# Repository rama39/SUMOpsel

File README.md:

# SUMOpsel
Projeto de eletrônica do processo seletivo do Maracatronics 2024.2/2025.1

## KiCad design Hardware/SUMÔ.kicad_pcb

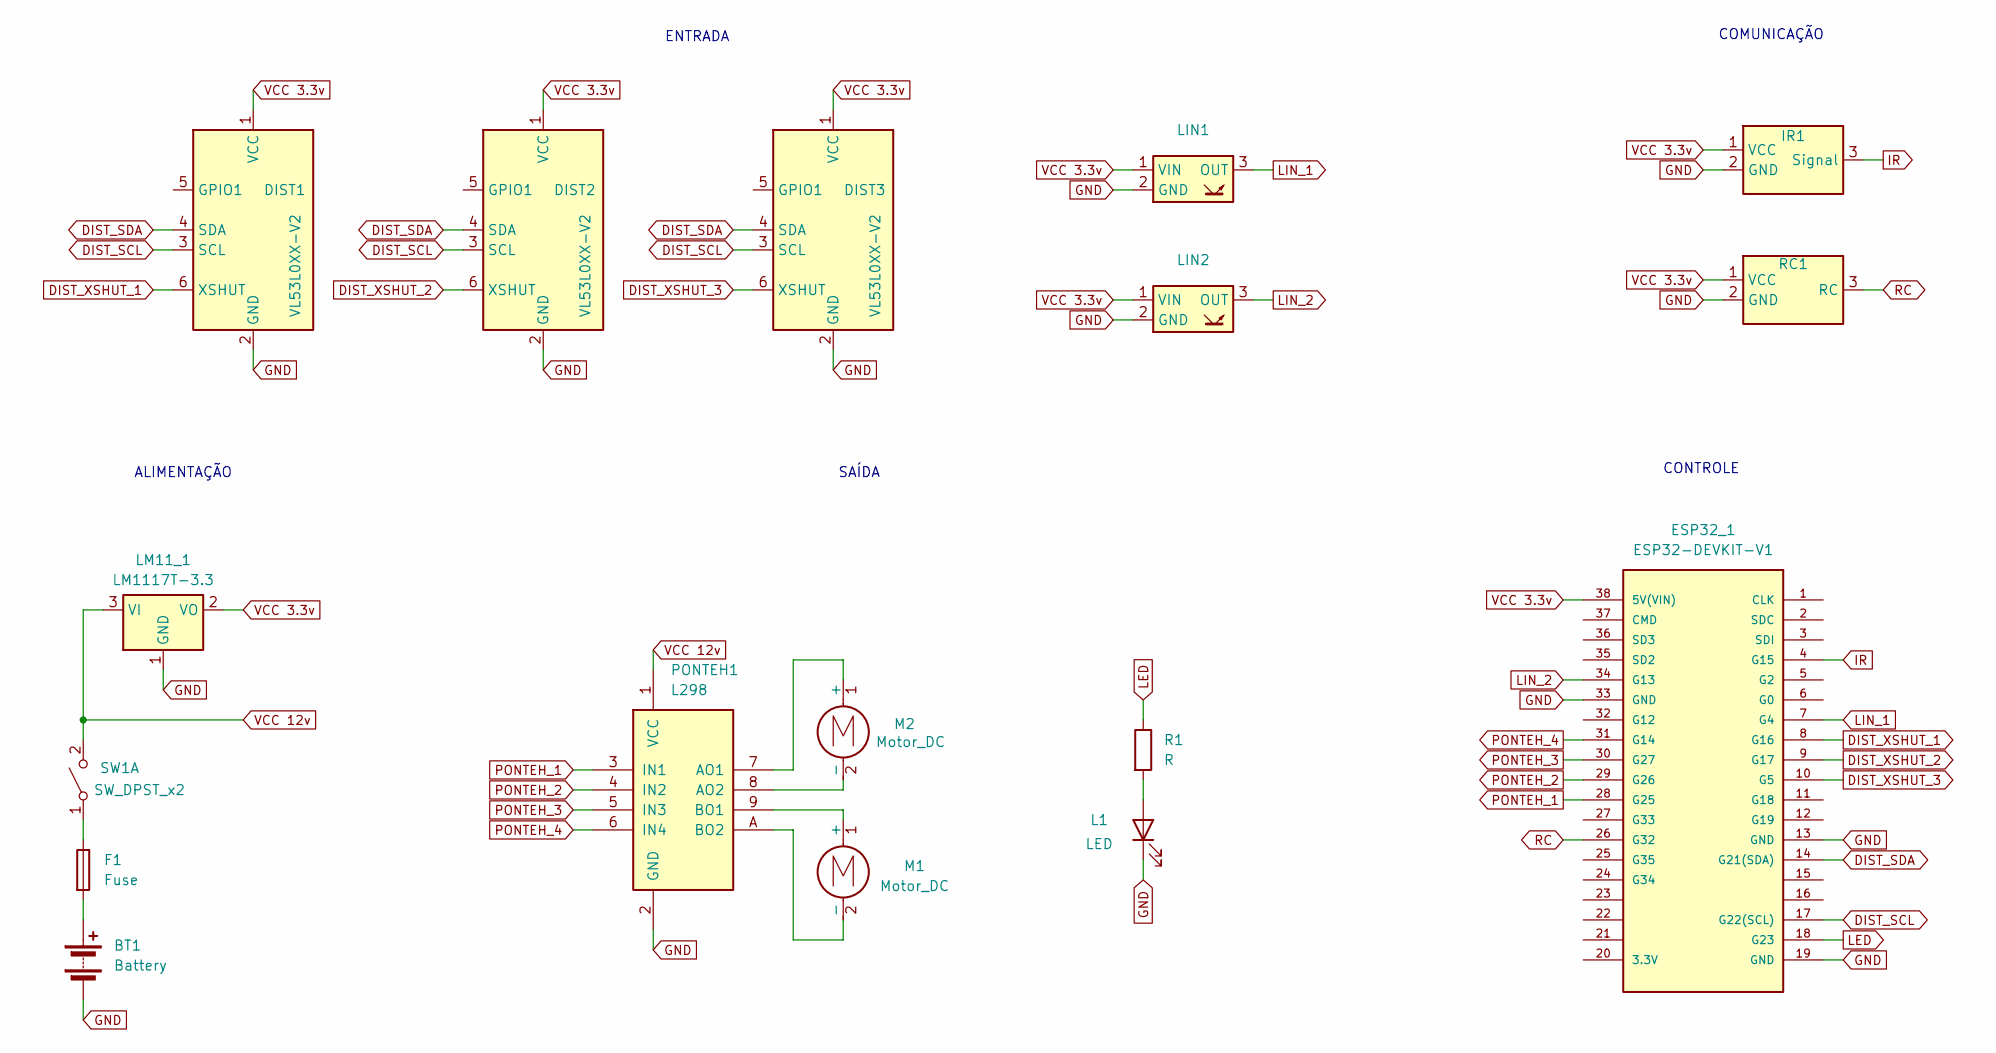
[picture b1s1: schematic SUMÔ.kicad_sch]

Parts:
BT1: Battery; PinHeader_1x02_P2.54mm_Vertical
DIST1, DIST2, DIST3: VL53L0XX-V2; Vl53l0x_custom
ESP32_1: ESP32-DEVKIT-V1; MODULE_ESP32_DEVKIT_V1; PARTREV N/A
F1: Fuse; Fuseholder_Clip-5x20mm_Littelfuse_100_Inline_P20.50x4.60mm_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
IR1: KY022_custom
L1: LED; LED_D3.0mm
LIN1, LIN2: QRE1113_custom
LM11_1: LM1117T-3.3; TO-220-3_Vertical
M1, M2: Motor_DC; PinHeader_1x02_P2.54mm_Vertical
PONTEH1: L298; PONTEH_custom
R1: R; R_Axial_DIN0204_L3.6mm_D1.6mm_P7.62mm_Horizontal
RC1: RC_custom
SW1: SW_DPST_x2; PinHeader_1x02_P2.54mm_Vertical

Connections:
DIST_SCL: DIST1.3 (SCL), DIST2.3 (SCL), DIST3.3 (SCL), ESP32_1.17 (G22(SCL))
DIST_SDA: DIST1.4 (SDA), DIST2.4 (SDA), DIST3.4 (SDA), ESP32_1.14 (G21(SDA))
DIST_XSHUT_1: DIST1.6 (XSHUT), ESP32_1.8 (G16)
DIST_XSHUT_2: DIST2.6 (XSHUT), ESP32_1.9 (G17)
DIST_XSHUT_3: DIST3.6 (XSHUT), ESP32_1.10 (G5)
GND: BT1.2 (-), DIST1.2 (GND), DIST2.2 (GND), DIST3.2 (GND), ESP32_1.13 (GND), ESP32_1.19 (GND), ESP32_1.33 (GND), IR1.2 (GND), L1.1 (K), LIN1.2 (GND), LIN2.2 (GND), LM11_1.1 (GND), PONTEH1.2 (GND), RC1.2 (GND)
IR: ESP32_1.4 (G15), IR1.3 (Signal)
LED: ESP32_1.18 (G23), R1.1
LIN_1: ESP32_1.7 (G4), LIN1.3 (OUT)
LIN_2: ESP32_1.34 (G13), LIN2.3 (OUT)
unnamed: BT1.1 (+), F1.2
unnamed: L1.2 (A), R1.2
unnamed: M1.1 (+), PONTEH1.9 (BO1)
unnamed: M1.2 (-), PONTEH1.A (BO2)
unnamed: M2.1 (+), PONTEH1.7 (AO1)
unnamed: M2.2 (-), PONTEH1.8 (AO2)
unnamed: F1.1, SW1.1 (A)
PONTEH_1: ESP32_1.28 (G25), PONTEH1.3 (IN1)
PONTEH_2: ESP32_1.29 (G26), PONTEH1.4 (IN2)
PONTEH_3: ESP32_1.30 (G27), PONTEH1.5 (IN3)
PONTEH_4: ESP32_1.31 (G14), PONTEH1.6 (IN4)
RC: ESP32_1.26 (G32), RC1.3 (RC)
VCC 3.3v: DIST1.1 (VCC), DIST2.1 (VCC), DIST3.1 (VCC), ESP32_1.38 (5V(VIN)), IR1.1 (VCC), LIN1.1 (VIN), LIN2.1 (VIN), LM11_1.2 (VO), RC1.1 (VCC)
VCC 12v: LM11_1.3 (VI), PONTEH1.1 (VCC), SW1.2 (B)

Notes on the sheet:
CONTROLE
SAÍDA
ENTRADA
ALIMENTAÇÃO
COMUNICAÇÃO

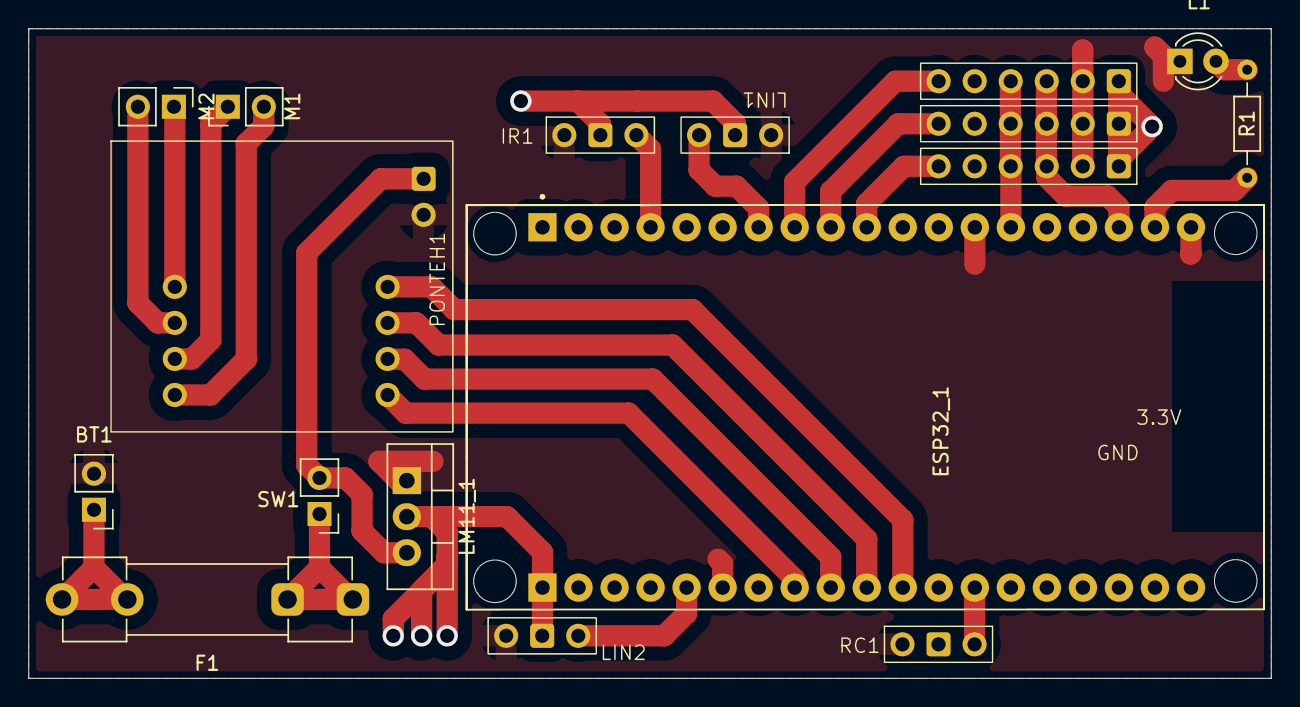
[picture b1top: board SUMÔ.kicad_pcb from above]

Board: 2 copper layers, 87.6 x 45.8 mm, 17 parts (0 on the bottom side), 24 nets.

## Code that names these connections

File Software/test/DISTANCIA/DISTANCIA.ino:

//================================================================================================
// Biblio dos VL53L0X
/*
  Biblioteca que controla a incialização e leitura de três sensores TOF VL53L0X
*/

// pin number 
#define DIST_XSHUT_1 5
#define DIST_XSHUT_2 17
#define DIST_XSHUT_3 16

// Usa biblioteca Adafruit como base
#include "Adafruit_VL53L0X.h"

// address we will assign sensors
#define LOX1_ADDRESS 0x30
#define LOX2_ADDRESS 0x31
#define LOX3_ADDRESS 0x32

void setupDist();

void setID();
void readSensores(bool);

//------------------------------------------------------------------------------------------------
/*
  Quase igual ao código encontrado em:
  https://github.com/adafruit/Adafruit_VL53L0X/blob/master/examples/vl53l0x_dual/vl53l0x_dual.ino
  <3 obg comunidade open source 🤝 <3
*/

// objects for the vl53l0x
Adafruit_VL53L0X lox1 = Adafruit_VL53L0X();
Adafruit_VL53L0X lox2 = Adafruit_VL53L0X();
Adafruit_VL53L0X lox3 = Adafruit_VL53L0X();

// this holds the measurement
VL53L0X_RangingMeasurementData_t measure1;
VL53L0X_RangingMeasurementData_t measure2;
VL53L0X_RangingMeasurementData_t measure3;

void setupDist();
void readDist();
void _printDistInd(string nome, VL53L0X_RangingMeasurementData_t &);
void printDist();

void setupDist() {
  
  // Configura pinos xshut
  pinMode(DIST_XSHUT_1, OUTPUT);
  pinMode(DIST_XSHUT_2, OUTPUT);
  pinMode(DIST_XSHUT_3, OUTPUT);
  
  // Configura I2C
  Wire.begin(21, 22); 

  // Configura ID de cada sensor VL53L0X

  // all reset
  digitalWrite(DIST_XSHUT_1, LOW);    
  digitalWrite(DIST_XSHUT_2, LOW);
  digitalWrite(DIST_XSHUT_3, LOW);
  delay(10);
  // all unreset
  digitalWrite(DIST_XSHUT_1, HIGH);
  digitalWrite(DIST_XSHUT_2, HIGH);
  digitalWrite(DIST_XSHUT_3, HIGH);
  delay(10);

  // activating LOX1 and resetting LOX2 and LOX3
  digitalWrite(DIST_XSHUT_1, HIGH);
  digitalWrite(DIST_XSHUT_2, LOW);
  digitalWrite(DIST_XSHUT_3, LOW);
  // initing LOX1
  if(!lox1.begin(LOX1_ADDRESS)) {
    Serial.println(F("Failed to boot first VL53L0X"));
    while(1);
  }
  delay(10);

  // activating LOX2
  digitalWrite(DIST_XSHUT_2, HIGH);
  delay(10);
  //initing LOX2
  if(!lox2.begin(LOX2_ADDRESS)) {
    Serial.println(F("Failed to boot second VL53L0X"));
    while(1);
  }

  // activating LOX3
  digitalWrite(DIST_XSHUT_3, HIGH);
  delay(10);
  //initing LOX3
  if(!lox3.begin(LOX3_ADDRESS)) {
    Serial.println(F("Failed to boot third VL53L0X"));
    while(1);
  }
}

void readDist() {
  
  lox1.rangingTest(&measure1, false); // pass in 'true' to get debug data printout!
  lox2.rangingTest(&measure2, false); // pass in 'true' to get debug data printout!
  lox3.rangingTest(&measure3, false); // pass in 'true' to get debug data printout!

}

void _printDistInd(string nome, VL53L0X_RangingMeasurementData_t &measurex) {

  // print sensor reading
  Serial.print(nome);
  Serial.print(": ");
  if(measurex.RangeStatus != 4) {     // if not out of range
    Serial.print(measurex.RangeMilliMeter);
  } else {
    Serial.print("Out of range");
  }
  
  Serial.print(" ");
}
void printDist() {

  // print sensor one reading
  _printDistInd("1", measure1);

  // print sensor two reading
  _printDistInd("2", measure2);

  // print sensor three reading
  _printDistInd("3", measure3);
  
  Serial.println();

}

//================================================================================================

void setup() {
  
  Serial.begin(9600);

  setupDist();

}

void loop() {

  readDist();
  printDist();
  delay(10);

}

//================================================================================================

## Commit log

2025-04-18 V1: init
2025-04-18 V1: (feat) leitura dist mm
2025-04-18 V1: (feat) controle init funcoes
2025-04-18 V1: (feat:lin) funcoes por sensor
2025-04-18 V1: (main) init
2025-04-24 V1: (refactor:lib) consertar
2025-05-19 V1: (feat:teste geral) update todos componentes
2025-05-19 V1: (feat:teste) update todos testes individuais
2025-05-19 V3: (circuito) update Hardware
2025-05-19 V2: (fluxograma) update
